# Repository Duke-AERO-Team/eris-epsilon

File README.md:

Note: This README is incomplete
Whether or not we use KiCad is also undecided.

# Eris Epsilon PCB
Eris Epsilon is the 5th version of Duke AERO's SRAD flight computer ERIS.

## Usage
This year, we are switching to KiCAD for PCB design. Previous years have used Eagle. The Eagle files and datasheet for ERIS Delta are available in the Google Drive under `2024/2025 Aero>Avionics>Eris Delta`.

### KiCad Setup
To install KiCad see [here](https://www.kicad.org/)

### Git Workflow
#### Getting this project
1. Make sure you have Git installed
2. In the terminal, navigate to the directory where you want to have this project
* You can sometimes do so by opening the folder, right clicking, and clicking "open in terminal/open in powershell"
* Otherwise, navigate to the directory in your file explorer. Copy the path. Open terminal (Mac), cmd, or powershell (Windows) and enter `cd <directory`.
3. Run `git clone git@github.com:Duke-AERO-Team/eris-epsilon.git`

#### Making changes
##### You haven't made any changes yet
1. Run `git branch <change_title>`
2. Run `git switch <change_title>`
3. Make your changes
4. Run `git add .` or add each file you changed one by one
5. Run `git commit "description of your changes"
6. Run `git push --set-upstream origin <change_title>`
7. See "merging" below

##### Merging
In the past, I have been horrible with version control! No longer. To make your changes a part of the official schematic, you must make the changes in a separate branch, make a pull request, and have someone verify your changes before merging.

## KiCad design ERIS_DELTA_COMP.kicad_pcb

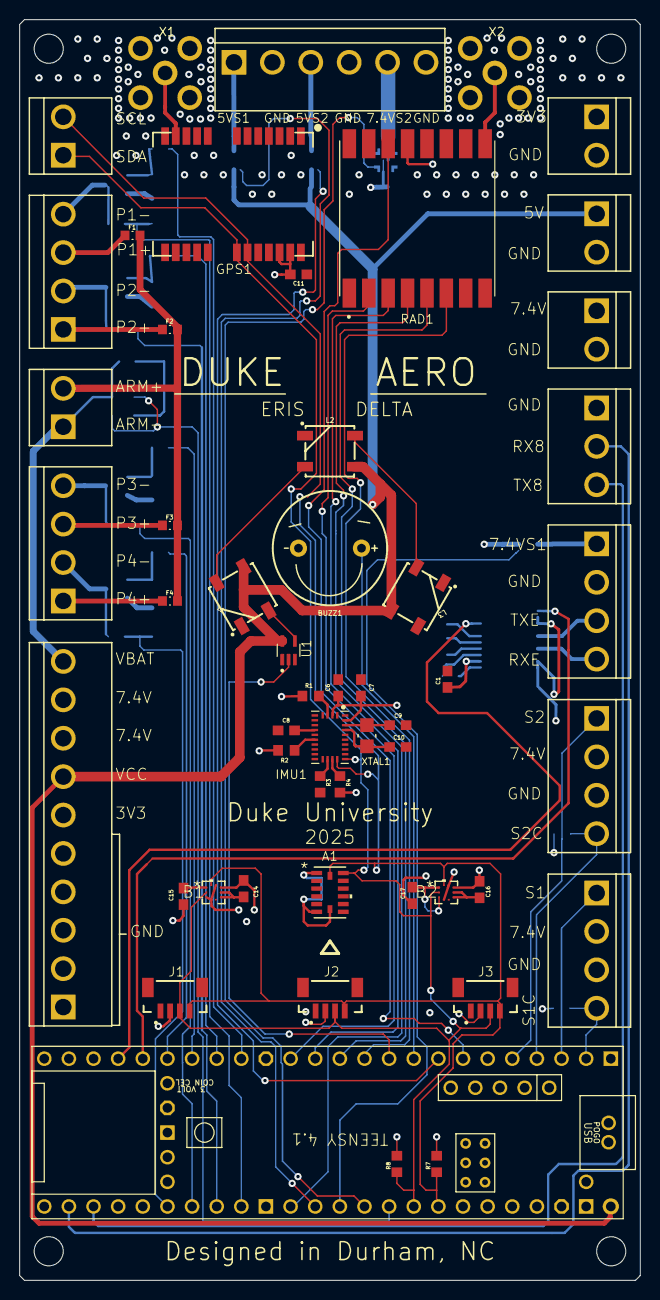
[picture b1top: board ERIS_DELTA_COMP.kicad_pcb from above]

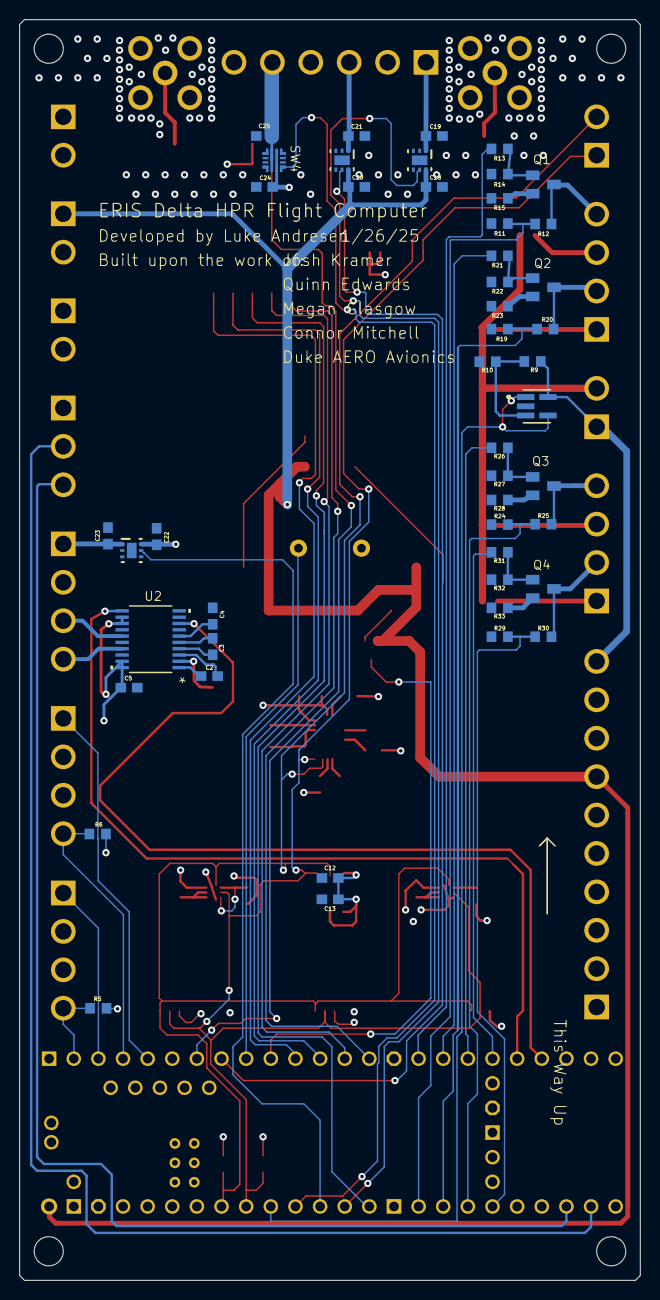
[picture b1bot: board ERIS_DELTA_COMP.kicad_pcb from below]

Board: 4 copper layers, 64.0 x 130.0 mm, 104 parts (48 on the bottom side), 78 nets.

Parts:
@HOLE0, @HOLE1, @HOLE2, @HOLE3: (no value)
A1: ADXL375BCCZ-RL7; LGA_CC-14-1_ADI
B1, B2: BMP390LGA10_BMP390_BOS-L; LGA10_BMP390_BOS-L
BUZZ1: BUZZER-PTH; BUZZER-12MM
C1, C2, C3, C4, C5, C6, C7, C8, C13, C14, C15, C16, C17: 100nF; C0603_334
C9, C10: 22pF; C0603_334
C11, C18, C20, C22, C24, C25: 1uF; C0603_334
C12: 10uF; C0603_334
C19, C21, C23: 0.1uF; C0603_334
CN1, CN2, CN3, CN4, CN5: B4P-VH
CN6: B3P-VH
CN7, CN8, CN9, CN10, CN11: B2P-VH
CN12: B10P-VH
CN13: B6P-VH
F1, F2, F3, F4: 0686F3000-01; FUSC1608X60N
GPS1: U-BLOX_NEO-M9N; NEO-M9N_M8T_M8U_D9S_F9P_518
IMU1: BNO08X_PKG_vf.XGgjGLvfRIem9WPZyf6Beg
J1, J2, J3: Vertical Qwiic Connector; JST04_1MM_VERT
L1, L2, L3: WS2812B
Q1, Q2, Q3, Q4: SOT23
R1, R2, R3, R4, R5, R6, R10: 10k; R0603_334
R7, R8: 4.7k; R0603_334
R9: 62k; R0603_334
R11, R19, R24, R29: 100k; R0603_334
R12, R20, R25, R30: 470k; R0603_334
R13, R21, R26, R31: 1k; R0603_334
R14, R22, R27, R32: 47k; R0603_334
R15, R23, R28, R33: 1; R0603_334
RAD1: RFM95W-915S2; XCVR_RFM95W-915S2
SW1, SW2, SW3: TPS22810DRVRDRV0006A_NV; DRV0006A_NV_vf.FMRw0siSRJu5t1qxaqj72w
SW4: PTPS22811LRPWR; VQFN10_RPW_TEX
U1: SN74AHCT1G125DCKT; SOT65P210X110-5N
U2: MAX3380EEUP+21-0066J_20_MXM; 21-0066J_20_MXM_46576824
U6: OPA990IDBVR; DBV0005A-IPC_A
U$1: TEENSY41
X1, X2: SMA90_DIP_420
XTAL1: RT3215-32.768-12.5-TR; RT3215_RAL

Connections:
3V3: A1.1, A1.6, A1.7, B1.1, B1.5, B1.6, B1.10, B2.1, B2.6, B2.10, C5.1, C6.1, C7.1, C11.1, C12.1, C13.1, C14.1, C15.1, C16.1, C17.1, CN8.1, CN12.6, GPS1.22, GPS1.23, IMU1.2, IMU1.27, J1.2, J2.2, J3.2, R1.1, R2.1, R4.2, R5.2, R6.2, R7.2, R8.2, RAD1.13, U2.12, U2.13, U2.19, U2.20
5VS1: C19.1, CN13.1, SW1.1
5VS2: C21.1, CN13.3, SW2.1
7.4V: C22.1, C24.1, CN1.2, CN2.2, CN9.1, CN12.8, CN12.9, SW3.6, SW4.5
7.4VS1: C23.1, CN5.1, SW3.1
7.4VS2: C25.1, CN13.5, SW4.6
ARM: CN11.2, F1.1, F2.1, F3.1, F4.1
BATT-READ: U6.1, U6.4, U$1.17-A3/TX4/SDA1
BAT_DIV: R9.2, R10.1, U6.3
BUZZ: BUZZ1.+, U$1.7-RX2/OUT1A
CS-RF: RAD1.5, U$1.10-CS\MQSR
GND: A1.12, B1.3, B1.8, B1.9, B2.3, B2.5, B2.8, B2.9, BUZZ1.-, C1.2, C4.1, C5.2, C6.2, C7.2, C8.2, C9.2, C10.2, C11.2, C12.2, C13.2, C14.2, C15.2, C16.2, C17.2, C18.2, C19.2, C20.2, C21.2, C22.2, C23.2, C24.2, C25.2, CN1.3, CN2.3, CN5.2, CN6.1, CN7.2, CN8.2, CN9.2, CN12.1, CN12.2, CN12.3, CN12.4, CN12.5, CN13.2, CN13.4, CN13.6, GPS1.7, GPS1.10, GPS1.12, GPS1.13, GPS1.24, IMU1.1, IMU1.4, IMU1.5, IMU1.9, IMU1.24, J1.1, J2.1, J3.1, L1.3, L2.3, L3.3, R3.2, R10.2, R11.1, R14.2, R15.2, R19.1, R22.2, R23.2, R24.1, R27.2, R28.2, R29.1, R32.2, R33.2, RAD1.1, RAD1.8, RAD1.10, SW1.4, SW1.7, SW2.4, SW2.7, SW3.4, SW3.7, SW4.8, U1.1, U1.3, U2.18, U6.2, U$1.GND1, U$1.GND2, U$1.GND3, U$1.GND4, U$1.GND5, U$1.GND6, X1.GND1, X1.GND2, X1.GND3, X1.GND4, X2.GND1, X2.GND2, X2.GND3, X2.GND4
GPS-ANT: GPS1.11, X1.ANTENNA
IRQ: RAD1.14, U$1.5-IN2
LED: U1.2, U$1.8-TX2/IN2
LSHIFT: L1.4, U1.4
MISO: RAD1.2, U$1.12-MISO/MQSL
MOSI: RAD1.3, U$1.11-MOSI/CTX1
unnamed: C8.1, IMU1.8
unnamed: Q2.1, R21.1, R22.1
unnamed: Q2.2, R23.1
unnamed: Q3.1, R26.1, R27.1
unnamed: Q3.2, R28.1
unnamed: Q4.1, R31.1, R32.1
unnamed: C10.1, IMU1.25, XTAL1.1
unnamed: Q4.2, R33.1
unnamed: C9.1, IMU1.26, XTAL1.2
unnamed: IMU1.16, R3.1
unnamed: IMU1.17, R4.1
unnamed: IMU1.10, R2.2
unnamed: IMU1.3, R1.2
unnamed: C2.2, U2.3
unnamed: C1.1, U2.2
unnamed: C3.1, U2.4
unnamed: Q1.1, R13.1, R14.1
unnamed: C3.2, U2.5
unnamed: C4.2, U2.6
unnamed: Q1.2, R15.1
unnamed: L1.2, L2.4
unnamed: L2.2, L3.4
P1+: CN4.3, F1.2
P1-: CN4.4, Q1.3, R12.2
P2+: CN4.1, F2.2
P2-: CN4.2, Q2.3, R20.2
P3+: CN3.3, F3.2
P3-: CN3.4, Q3.3, R25.2
P4+: CN3.1, F4.2
P4-: CN3.2, Q4.3, R30.2
PYRO1-CONT: R11.2, R12.1, U$1.41-A17/MISO1
PYRO1-FIRE: R13.2, U$1.24-A10/TX6/SCL2
PYRO2-CONT: R19.2, R20.1, U$1.40-A16/CS1
PYRO2-FIRE: R21.2, U$1.25-A11/RX6/SDA2
PYRO3-CONT: R24.2, R25.1, U$1.39-A15/CS/OUT1A
PYRO3-FIRE: R26.2, U$1.26-A12/MOSI1
PYRO4-CONT: R29.2, R30.1, U$1.38-A14/CS/IN1
PYRO4-FIRE: R31.2, U$1.27-A13/SCK1
RF-ANT: RAD1.9, X2.ANTENNA
RRST: RAD1.6, U$1.9-OUT1C
RX7: U2.11, U$1.28-RX7
RX8: CN6.2, U$1.34-RX8
RXE: CN5.4, U2.17
SCK: RAD1.4, U$1.13-SCK/LED
SCL: A1.14, B1.2, B2.2, CN10.2, GPS1.19, IMU1.18, J1.4, J2.4, J3.4, R7.1, U$1.19-A5/SCL0
SDA: A1.13, B1.4, B2.4, CN10.1, GPS1.18, IMU1.19, J1.3, J2.3, J3.3, R8.1, U$1.18-A4/SDA0
SERVO1: CN1.1, U$1.1-TX1/MISO1/CTX2
SERVO1-CONT: CN1.4, R5.1, U$1.0-RX1/CS1/CRX2
SERVO2: CN2.1, U$1.3-LRCLK2
SERVO2-CONT: CN2.4, R6.1, U$1.2-OUT2
SW5V1: SW1.5, U$1.14-A0/TX3/SPDIF_OUT
SW5V2: SW2.5, U$1.6-OUT1D
SW7.4V1: SW3.5, U$1.15-A1/RX3/SPDIF_IN
SW7.4V2: SW4.1, U$1.16-A2/RX4/SCL1
TX7: U2.8, U$1.29-TX7
TX8: CN6.3, U$1.35-TX8
TXE: CN5.3, U2.15
U2: C2.1, U2.1
VBAT: CN11.1, CN12.10, R9.1, U6.5
VCC: C18.1, C20.1, CN7.1, CN12.7, L1.1, L2.1, L3.1, SW1.6, SW2.6, U1.5, U$1.VIN

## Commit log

2025-09-07 Basic readme
